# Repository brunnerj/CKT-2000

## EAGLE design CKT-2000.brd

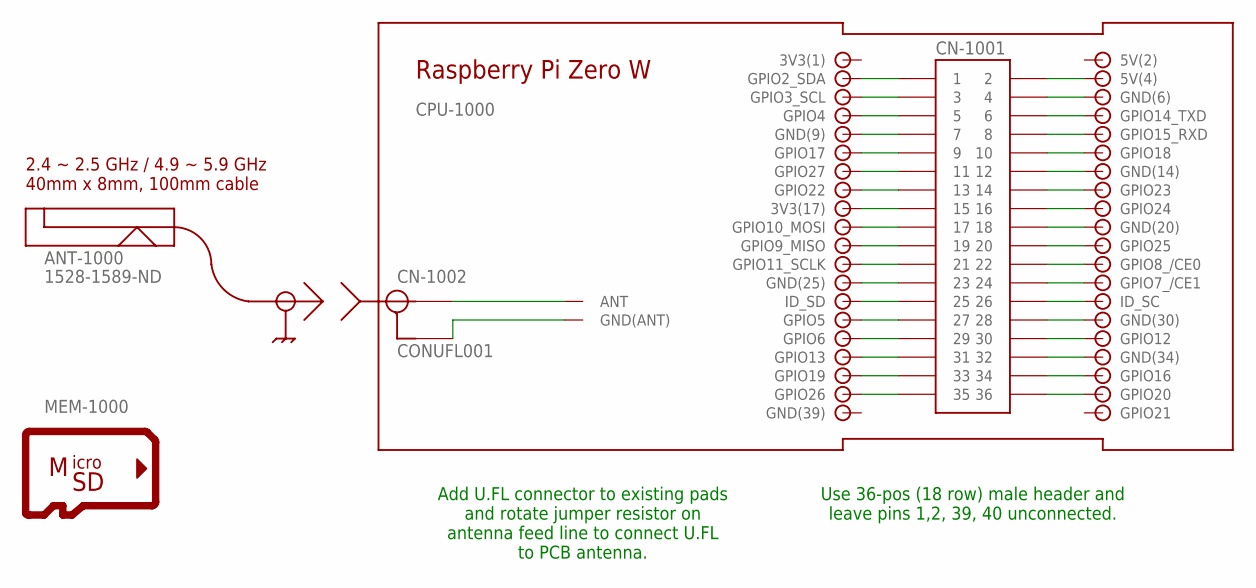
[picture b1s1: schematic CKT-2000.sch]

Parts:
CN-1001: HEADER-FE-2X18; HEADER-FE-2X18-TH
CN-1002: CONUFL001; CONUFL_UMC_SMD
CPU-1000: RASPBERRY_PI_ZERO_W

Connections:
3V3(1): CPU-1000.P$1 (3V3(1))
5V(2): CPU-1000.P$2 (5V(2))
GND(39): CPU-1000.P$39 (GND(39))
unnamed: CN-1001.P$1 (1), CPU-1000.P$3 (GPIO2_SDA)
unnamed: CN-1001.P$3 (3), CPU-1000.P$5 (GPIO3_SCL)
unnamed: CN-1001.P$5 (5), CPU-1000.P$7 (GPIO4)
unnamed: CN-1001.P$7 (7), CPU-1000.P$9 (GND(9))
unnamed: CN-1001.P$9 (9), CPU-1000.P$11 (GPIO17)
unnamed: CN-1001.P$11 (11), CPU-1000.P$13 (GPIO27)
unnamed: CN-1001.P$13 (13), CPU-1000.P$15 (GPIO22)
unnamed: CN-1001.P$15 (15), CPU-1000.P$17 (3V3(17))
unnamed: CN-1001.P$17 (17), CPU-1000.P$19 (GPIO10_MOSI)
unnamed: CN-1001.P$19 (19), CPU-1000.P$21 (GPIO9_MISO)
unnamed: CN-1001.P$21 (21), CPU-1000.P$23 (GPIO11_SCLK)
unnamed: CN-1001.P$23 (23), CPU-1000.P$25 (GND(25))
unnamed: CN-1001.P$25 (25), CPU-1000.P$27 (ID_SD)
unnamed: CN-1001.P$27 (27), CPU-1000.P$29 (GPIO5)
unnamed: CN-1001.P$29 (29), CPU-1000.P$31 (GPIO6)
unnamed: CN-1001.P$31 (31), CPU-1000.P$33 (GPIO13)
unnamed: CN-1001.P$33 (33), CPU-1000.P$35 (GPIO19)
unnamed: CN-1001.P$35 (35), CPU-1000.P$37 (GPIO26)
unnamed: CN-1001.P$2 (2), CPU-1000.P$4 (5V(4))
unnamed: CN-1001.P$4 (4), CPU-1000.P$6 (GND(6))
unnamed: CN-1001.P$6 (6), CPU-1000.P$8 (GPIO14_TXD)
unnamed: CN-1001.P$8 (8), CPU-1000.P$10 (GPIO15_RXD)
unnamed: CN-1001.P$10 (10), CPU-1000.P$12 (GPIO18)
unnamed: CN-1001.P$12 (12), CPU-1000.P$14 (GND(14))
unnamed: CN-1001.P$14 (14), CPU-1000.P$16 (GPIO23)
unnamed: CN-1001.P$16 (16), CPU-1000.P$18 (GPIO24)
unnamed: CN-1001.P$18 (18), CPU-1000.P$20 (GND(20))
unnamed: CN-1001.P$20 (20), CPU-1000.P$22 (GPIO25)
unnamed: CN-1001.P$22 (22), CPU-1000.P$24 (GPIO8_/CE0)
unnamed: CN-1001.P$24 (24), CPU-1000.P$26 (GPIO7_/CE1)
unnamed: CN-1001.P$26 (26), CPU-1000.P$28 (ID_SC)
unnamed: CN-1001.P$28 (28), CPU-1000.P$30 (GND(30))
unnamed: CN-1001.P$30 (30), CPU-1000.P$32 (GPIO12)
unnamed: CN-1001.P$32 (32), CPU-1000.P$34 (GND(34))
unnamed: CN-1001.P$34 (34), CPU-1000.P$36 (GPIO16)
unnamed: CN-1001.P$36 (36), CPU-1000.P$38 (GPIO20)
unnamed: CN-1002.P$1, CPU-1000.P$41 (ANT)
unnamed: CN-1002.P$2, CN-1002.P$3, CPU-1000.P$42 (GND(ANT)), CPU-1000.P$43 (GND(ANT))

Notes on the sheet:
Add U.FL connector to existing pads and rotate jumper resistor on antenna feed line to connect U.FL to PCB antenna.
Use 36-pos (18 row) male header and leave pins 1,2, 39, 40 unconnected.

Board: 2 copper layers, 3 parts (0 on the bottom side), 38 nets, no tracks yet.

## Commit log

2020-03-20 initial commit (starts at rev B)
